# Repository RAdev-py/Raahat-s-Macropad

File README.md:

# Raahat's Simple Macropad (Hackpad)

Welcome to the repository for my custom Macropad! It features 9 mechanical keys, a rotary encoder for volume/scrolling control, and an OLED screen.

Note: I used AI to help me whenever I got stuck with onshape cadding and I also used it to help me write up the firmware.

The firmware is powered by KMK.

## Project Gallery

### Overall Hackpad

### Schematic

### PCB Layout

---

## 🛠️ Bill of Materials (BOM)

Here is the complete list of components required to build the PCB for this macropad:

| Designator | Footprint | Quantity | Value |
|:---|:---|:---:|:---|
| D1, D2, D3, D4, D5, D6, D7, D8, D9 | `D_DO-35_SOD27_P7.62mm_Horizontal` | 9 | 1N4148 |
| J1 | `FanPinHeader_1x04_P2.54mm_Vertical` | 1 | Conn_01x04 |
| SW1, SW2, SW3, SW4, SW5, SW6, SW7, SW8, SW9 | `SW_Cherry_MX_1.00u_PCB` | 9 | SW_Push |
| SW10 | `RotaryEncoder_Alps_EC11E-Switch_Vertical_H20mm` | 1 | RotaryEncoder_Switch |
| U1 | `XIAO-Generic-Hybrid-14P-2.54-21X17.8MM` | 1 | MODULE-SEEEDUINO-XIAO |

### Additional Hardware:
* **Microcontroller:** 1x Seeed Studio XIAO (RP2040, SAMD21, or similar)
* **Switches:** 9x Cherry MX-compatible mechanical switches (3-pin or 5-pin)
* **Keycaps:** 9x 1U Keycaps
* **Encoder Knob:** 1x Knob compatible with standard EC11 rotary encoders
* **Screen:** 1x 0.91" or 0.96" I2C OLED Display
* **Fasteners:** M3 Heat-set inserts & M3 Screws (for the 3D printed case)

---

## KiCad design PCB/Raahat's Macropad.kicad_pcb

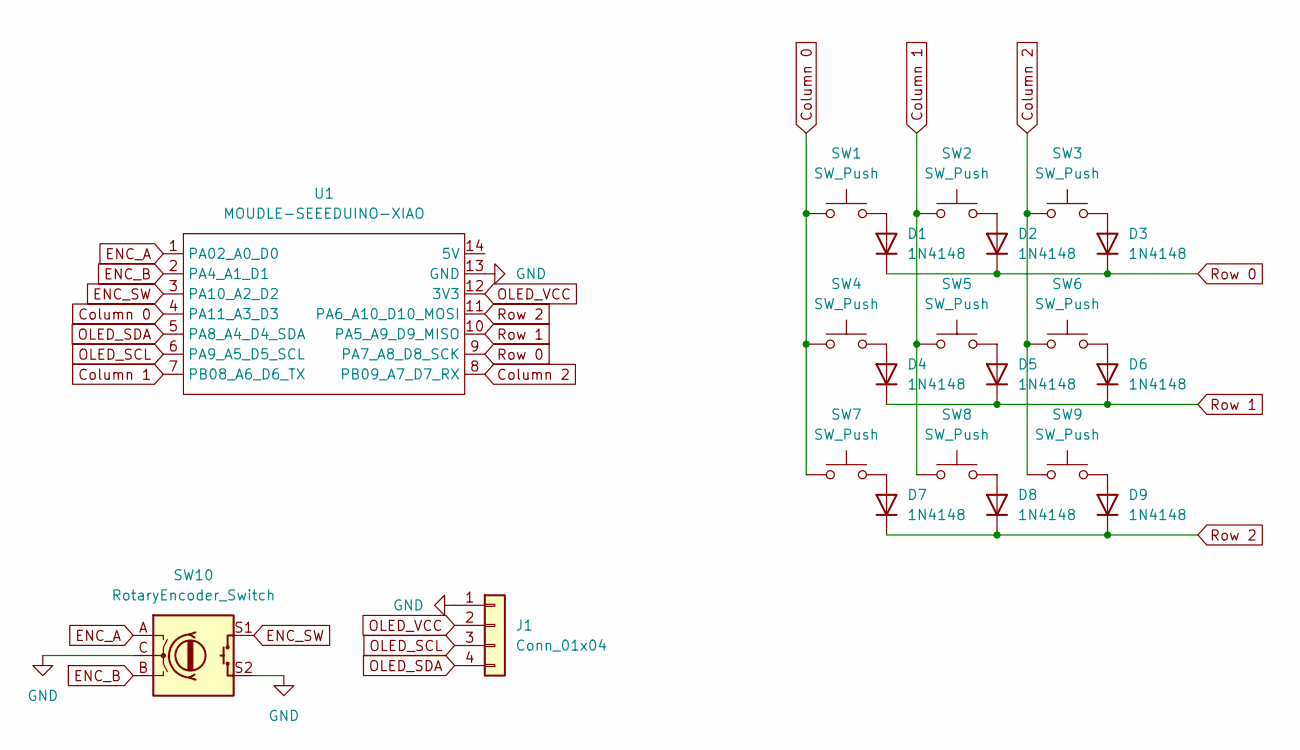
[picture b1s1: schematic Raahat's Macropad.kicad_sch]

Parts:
D1, D2, D3, D4, D5, D6, D7, D8, D9: 1N4148; D_DO-35_SOD27_P7.62mm_Horizontal
J1: Conn_01x04; FanPinHeader_1x04_P2.54mm_Vertical
SW1, SW2, SW3, SW4, SW5, SW6, SW7, SW8, SW9: SW_Push; SW_Cherry_MX_1.00u_PCB
SW10: RotaryEncoder_Switch; RotaryEncoder_Alps_EC11E-Switch_Vertical_H20mm
U1: MOUDLE-SEEEDUINO-XIAO; XIAO-Generic-Hybrid-14P-2.54-21X17.8MM

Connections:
Column 0: SW1.1, SW4.1, SW7.1, U1.4 (PA11_A3_D3)
Column 1: SW2.1, SW5.1, SW8.1, U1.7 (PB08_A6_D6_TX)
Column 2: SW3.1, SW6.1, SW9.1, U1.8 (PB09_A7_D7_RX)
ENC_A: SW10.A, U1.1 (PA02_A0_D0)
ENC_B: SW10.B, U1.2 (PA4_A1_D1)
ENC_SW: SW10.S1, U1.3 (PA10_A2_D2)
GND: J1.1, SW10.C, SW10.S2, U1.13 (GND)
unnamed: D1.2 (A), SW1.2
unnamed: D2.2 (A), SW2.2
unnamed: D3.2 (A), SW3.2
unnamed: D4.2 (A), SW4.2
unnamed: D5.2 (A), SW5.2
unnamed: D6.2 (A), SW6.2
unnamed: D7.2 (A), SW7.2
unnamed: D8.2 (A), SW8.2
unnamed: D9.2 (A), SW9.2
OLED_SCL: J1.3, U1.6 (PA9_A5_D5_SCL)
OLED_SDA: J1.4, U1.5 (PA8_A4_D4_SDA)
OLED_VCC: J1.2, U1.12 (3V3)
Row 0: D1.1 (K), D2.1 (K), D3.1 (K), U1.9 (PA7_A8_D8_SCK)
Row 1: D4.1 (K), D5.1 (K), D6.1 (K), U1.10 (PA5_A9_D9_MISO)
Row 2: D7.1 (K), D8.1 (K), D9.1 (K), U1.11 (PA6_A10_D10_MOSI)

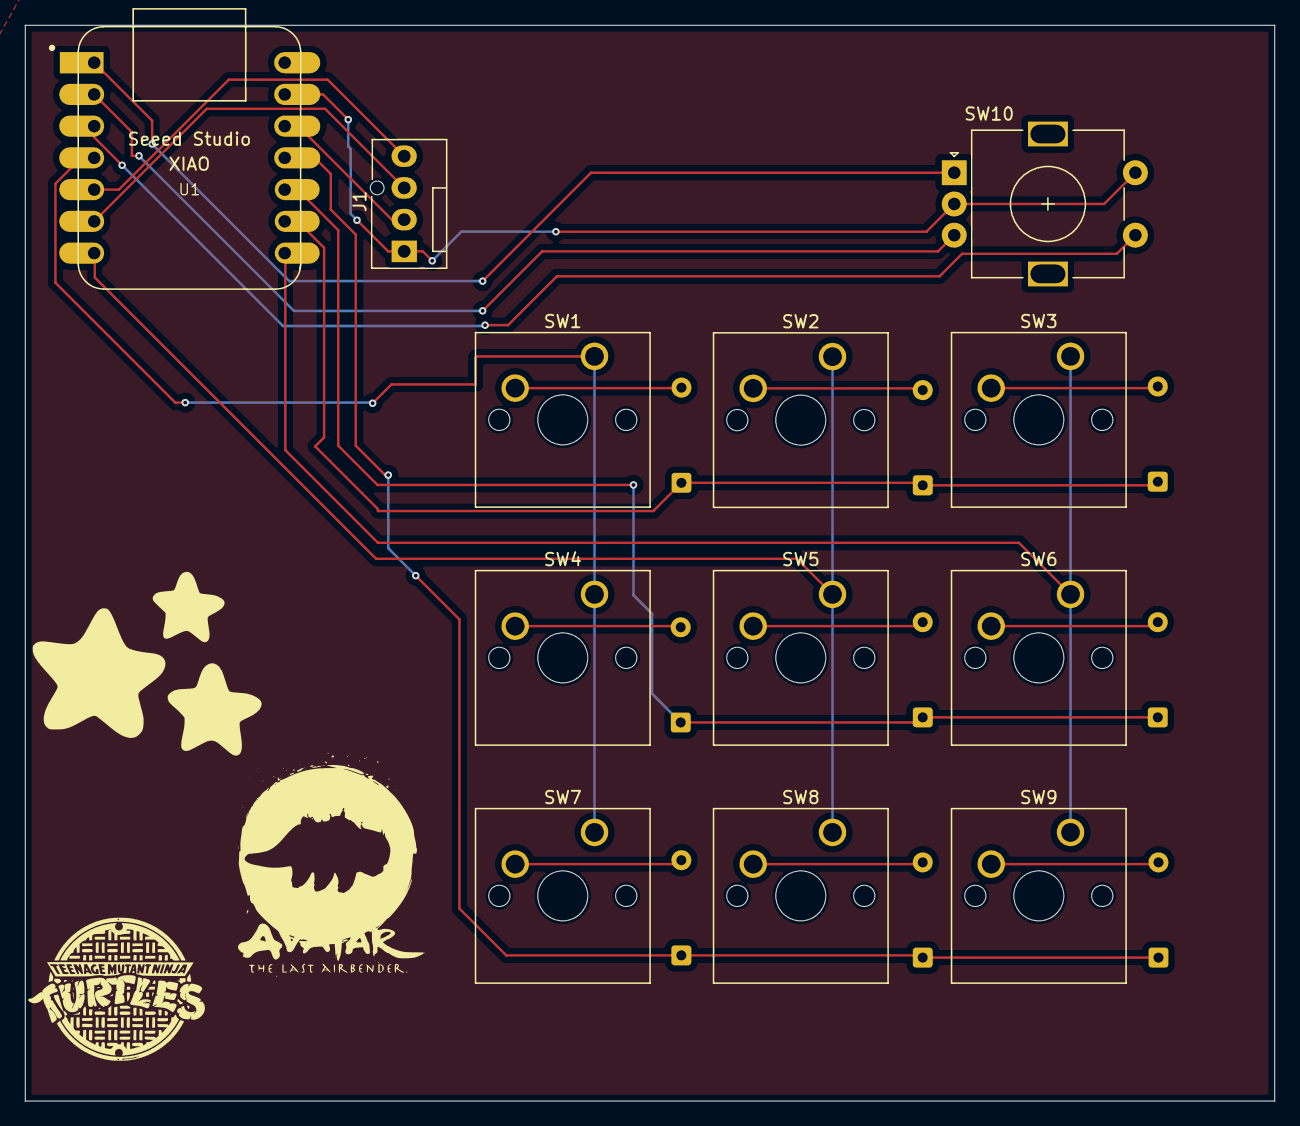
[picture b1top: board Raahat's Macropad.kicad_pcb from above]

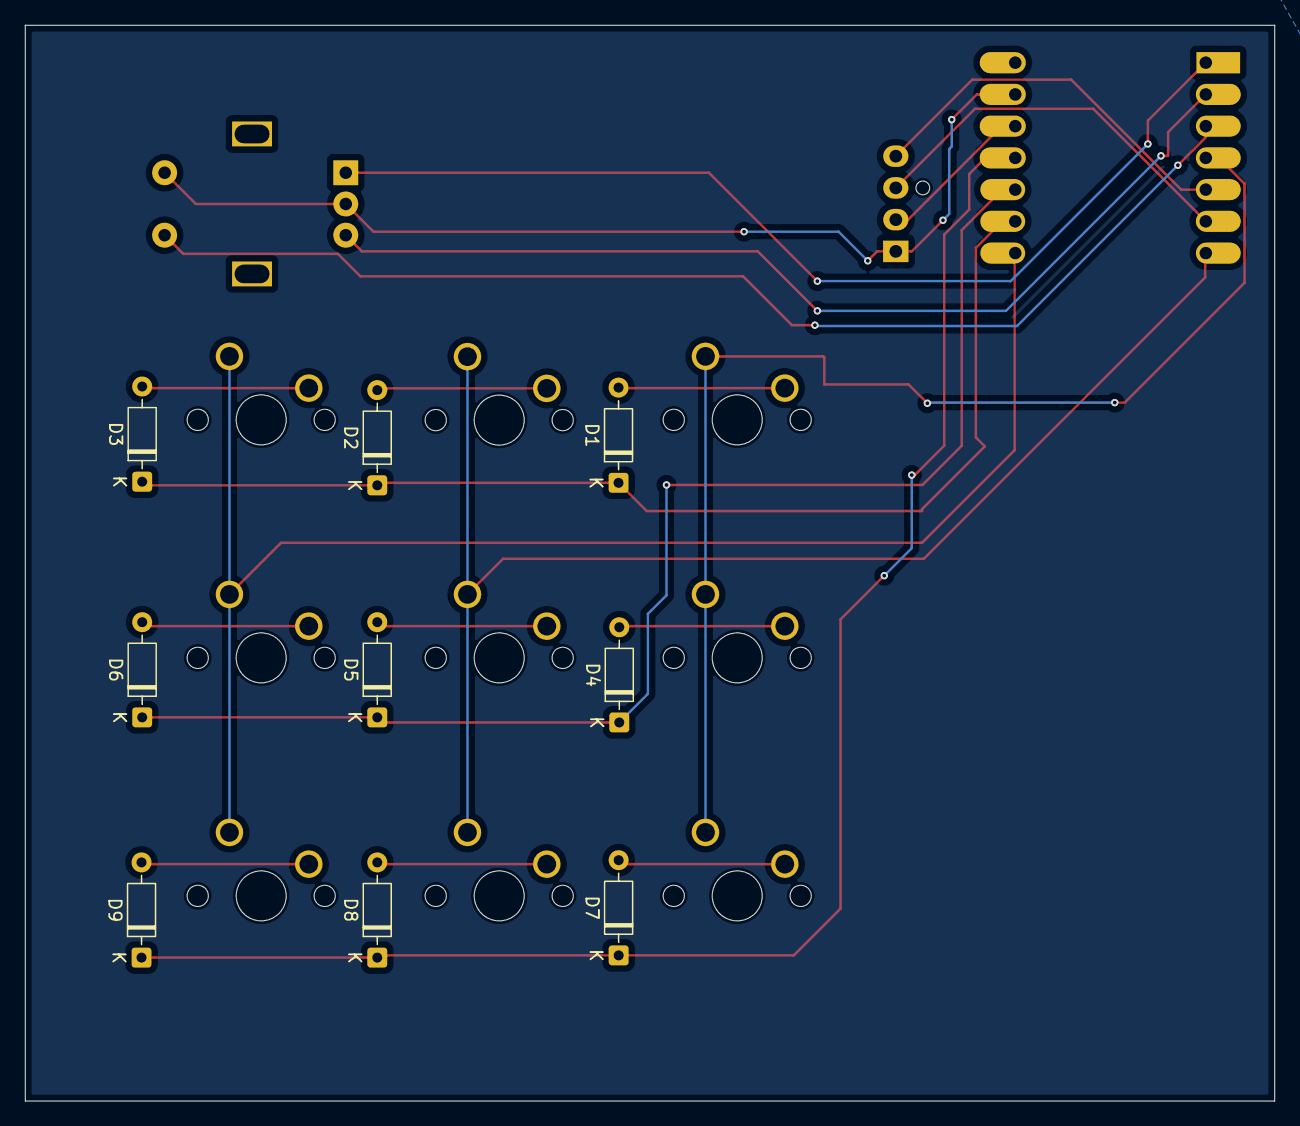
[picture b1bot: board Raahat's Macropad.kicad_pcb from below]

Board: 2 copper layers, 100.0 x 86.1 mm, 21 parts (9 on the bottom side), 22 nets.

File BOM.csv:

Designator,Footprint,Quantity,Value
"D1, D2, D3, D4, D5, D6, D7, D8, D9",D_DO-35_SOD27_P7.62mm_Horizontal,9,1N4148
J1,FanPinHeader_1x04_P2.54mm_Vertical,1,Conn_01x04
"SW1, SW2, SW3, SW4, SW5, SW6, SW7, SW8, SW9",SW_Cherry_MX_1.00u_PCB,9,SW_Push
SW10,RotaryEncoder_Alps_EC11E-Switch_Vertical_H20mm,1,RotaryEncoder_Switch
U1,XIAO-Generic-Hybrid-14P-2.54-21X17.8MM,1,MODULE-SEEEDUINO-XIAO

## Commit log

2026-06-18 added necessary files
2026-06-29 added bom csv file
